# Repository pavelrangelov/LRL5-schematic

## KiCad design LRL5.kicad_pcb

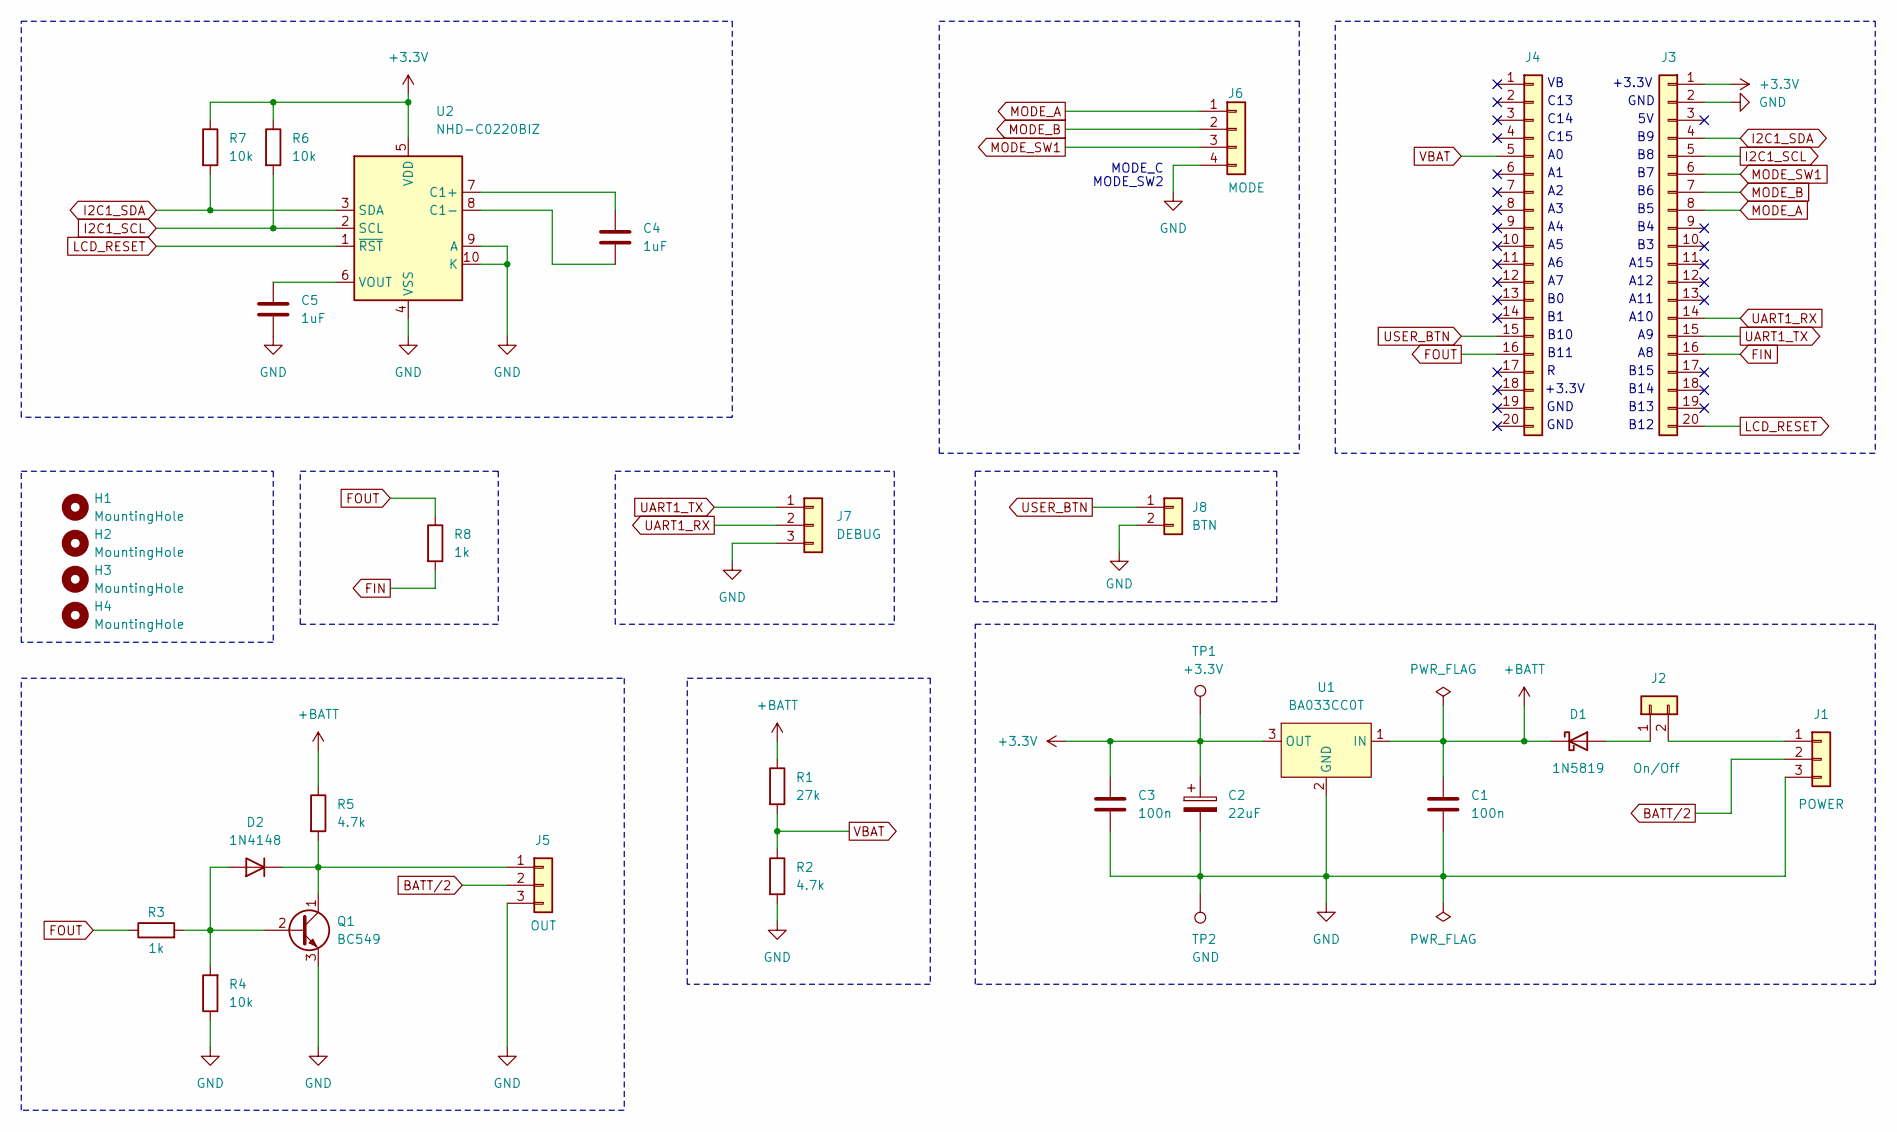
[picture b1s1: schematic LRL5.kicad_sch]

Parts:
C1, C3: 100n; C_0805_2012Metric_Pad1.18x1.45mm_HandSolder
C2: 22uF; CP_Radial_D5.0mm_P2.50mm
C4, C5: 1uF; C_0805_2012Metric_Pad1.18x1.45mm_HandSolder
D1: 1N5819; D_SMA_Handsoldering
D2: 1N4148; D_SMA_Handsoldering
H1, H2, H3, H4: MountingHole; MountingHole_3.2mm_M3
J1: POWER; PinHeader_1x03_P2.54mm_Vertical
J2: On/Off; PinHeader_1x02_P2.54mm_Vertical_SMD_Pin1Left
J3, J4: PinHeader_1x20_P2.54mm_Vertical_SMD_Pin1Left
J5: OUT; PinHeader_1x03_P2.54mm_Vertical_SMD_Pin1Left
J6: MODE; PinHeader_1x04_P2.54mm_Vertical
J7: DEBUG; PinHeader_1x03_P2.54mm_Vertical_SMD_Pin1Left
J8: BTN; PinHeader_1x02_P2.54mm_Vertical_SMD_Pin1Left
Q1: BC549; TO-126-3_Vertical
R1: 27k; R_0805_2012Metric_Pad1.20x1.40mm_HandSolder
R2, R5: 4.7k; R_0805_2012Metric_Pad1.20x1.40mm_HandSolder
R3, R8: 1k; R_0805_2012Metric_Pad1.20x1.40mm_HandSolder
R4, R6, R7: 10k; R_0805_2012Metric_Pad1.20x1.40mm_HandSolder
TP1: +3.3V; TestPoint_THTPad_2.0x2.0mm_Drill1.0mm
TP2: GND; TestPoint_THTPad_2.0x2.0mm_Drill1.0mm
U1: BA033CC0T; TO-220F-3_Horizontal_TabDown
U2: NHD-C0220BIZ; NHD-C0220BiZ

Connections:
+3.3V: C2.1, C3.1, J3.1, R6.1, R7.1, TP1.1, U1.3 (OUT), U2.5 (VDD)
+BATT: C1.1, D1.1 (K), R1.1, R5.1, U1.1 (IN)
BATT/2: J1.2, J5.2
FIN: J3.16, R8.2
FOUT: J4.16, R3.1, R8.1
GND: C1.2, C2.2, C3.2, C5.1, J1.3, J3.2, J5.3, J6.4, J7.3, J8.2, Q1.3 (E), R2.2, R4.1, TP2.1, U1.2 (GND), U2.4 (VSS), U2.9 (A), U2.10 (K)
I2C1_SCL: J3.5, R6.2, U2.2 (SCL)
I2C1_SDA: J3.4, R7.2, U2.3 (SDA)
LCD_RESET: J3.20, U2.1 (~RST)
MODE_A: J3.8, J6.1
MODE_B: J3.7, J6.2
MODE_SW1: J3.6, J6.3
unnamed: D1.2 (A), J2.1
unnamed: D2.2 (A), Q1.2 (B), R3.2, R4.2
unnamed: D2.1 (K), J5.1, Q1.1 (C), R5.2
unnamed: J1.1, J2.2
unnamed: C4.1, U2.7 (C1+)
unnamed: C4.2, U2.8 (C1-)
unnamed: C5.2, U2.6 (VOUT)
UART1_RX: J3.14, J7.2
UART1_TX: J3.15, J7.1
USER_BTN: J4.15, J8.1
VBAT: J4.5, R1.2, R2.1

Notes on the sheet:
A10
A15
C15
MODE_SW2
GND
B12
C14
+3.3V
B10
MODE_C
B14
B11
C13
A12
B13
A11
B15

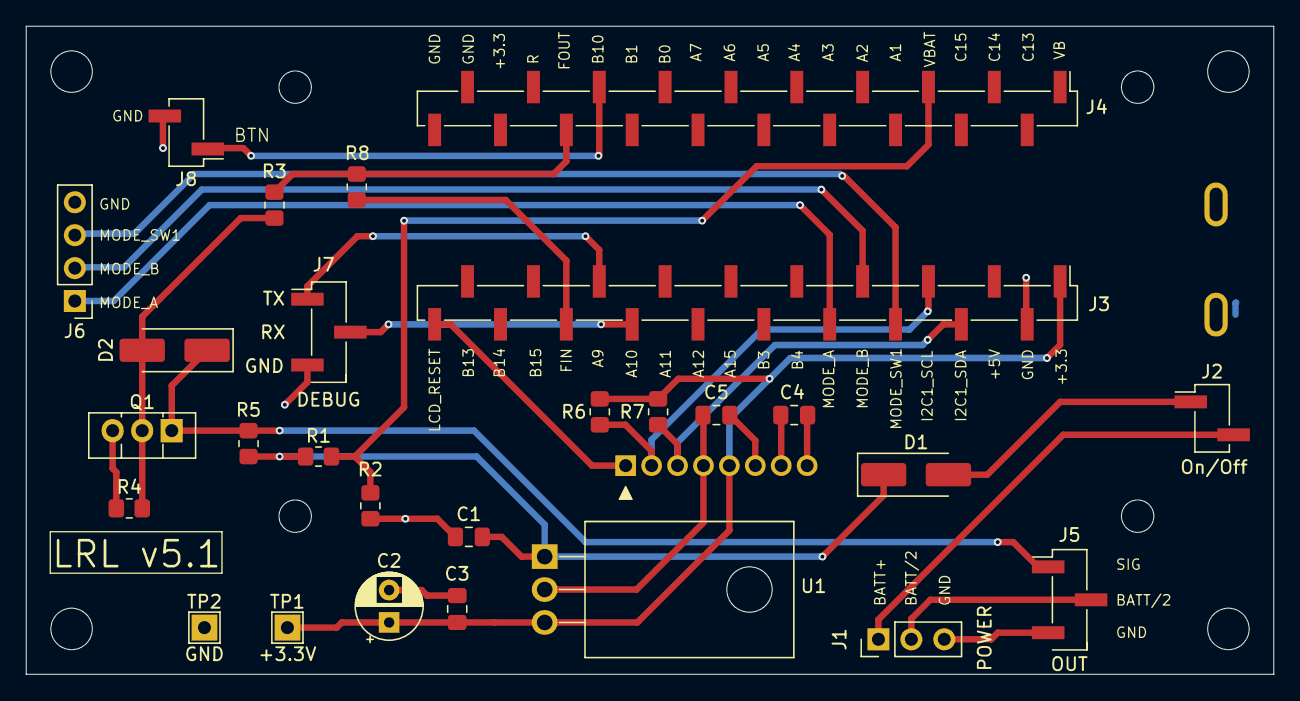
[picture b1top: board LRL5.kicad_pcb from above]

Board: 2 copper layers, 96.2 x 50.0 mm, 32 parts (1 on the bottom side), 23 nets.

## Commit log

2024-12-08 Fix some silkscreen overlaps
2024-12-08 Added filled zone
2024-12-08 Fix fill zone clearing
2024-12-09 Some PCB optimizations 1
2024-12-09 Redesign board for smaller size
2024-12-10 Some optimizations 2
2024-12-10 Change diodes footprints
2024-12-11 Redesign board. Move connectors
2024-12-11 Change some pins so thay don't interact with JTAG
2024-12-12 Remove ADJUST connector
2024-12-15 Some optimizations 3
2024-12-28 Fix LCD capacitor
2024-12-30 Generate manifacturing files
2024-12-31 Fix some wires
2025-01-30 Add selected box to documents
2025-02-09 Change BC549 footprint
2025-02-09 Change some texts
2025-02-14 Some fixes
2025-02-15 Some fixes 2
2025-02-15 Add DEBUG connector
2025-02-16 Fix version text
2025-02-17 Update some labels
2025-02-18 Add User Button
2025-02-18 Some changes
2025-03-05 Add profuction files
2025-04-01 Add wiring image
2025-08-20 Add screenshots
2025-08-20 Update screenshot
2025-08-20 Add LRL3 screenshot
